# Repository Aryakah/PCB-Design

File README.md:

Hello Everyone,

here i would publish my progress designing PCBs as a beginner. Hope it also helps you.

Im working on both Kicad and Altium projects, be sure you are pulling the right one:)

1 - Stm32f4 – Buck Converter 

2 - Stm32wb55 RF-Anwendung with USB-C 

3 - ESP32-S1 mini WIFI + Bluetooth (Altium)

4 - NRF24l01 Clone (added 04.11.2024)

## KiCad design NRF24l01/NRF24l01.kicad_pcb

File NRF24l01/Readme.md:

NRF24l01 PCB clone on Kicad. Schematics sourced from data Sheet.

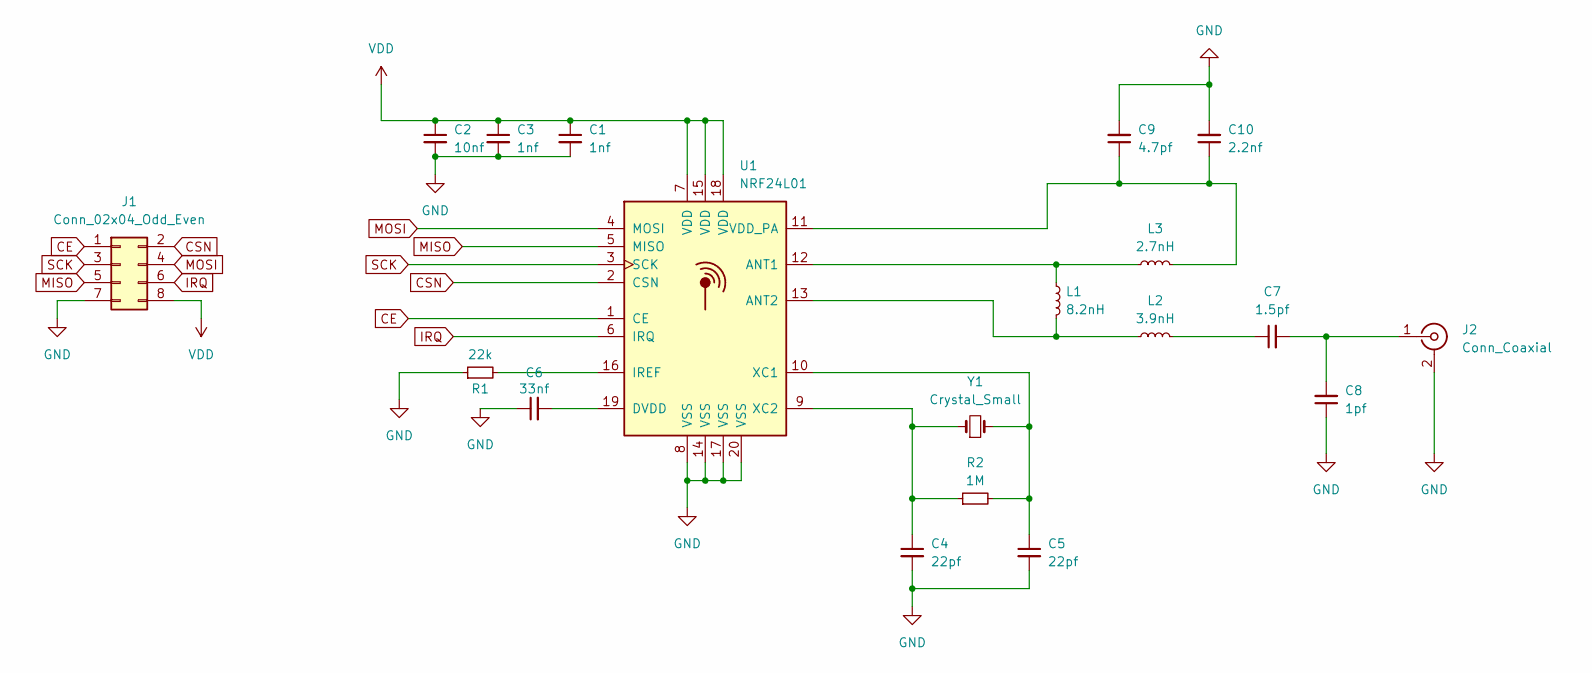
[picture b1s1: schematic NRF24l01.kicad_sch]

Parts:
C1, C3: 1nf; C_0402_1005Metric
C2: 10nf; C_0402_1005Metric
C4, C5: 22pf; C_0402_1005Metric
C6: 33nf; C_0402_1005Metric
C7: 1.5pf; C_0402_1005Metric
C8: 1pf; C_0402_1005Metric
C9: 4.7pf; C_0402_1005Metric
C10: 2.2nf; C_0402_1005Metric
J1: Conn_02x04_Odd_Even; PinHeader_2x04_P1.00mm_Vertical
J2: Conn_Coaxial; MMCX_Molex_73415-1471_Vertical
L1: 8.2nH; L_0402_1005Metric
L2: 3.9nH; L_0402_1005Metric
L3: 2.7nH; L_0402_1005Metric
R1: 22k; R_0402_1005Metric
R2: 1M; R_0402_1005Metric
U1: NRF24L01; QFN-20-1EP_4x4mm_P0.5mm_EP2.5x2.5mm
Y1: Crystal_Small; Crystal_SMD_HC49-SD

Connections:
CE: J1.1, U1.1 (CE)
CSN: J1.2, U1.2 (CSN)
GND: C1.2, C2.2, C3.2, C4.2, C5.2, C6.1, C8.1, C9.2, C10.2, J1.7, J2.2 (Ext), R1.1, U1.8 (VSS), U1.14 (VSS), U1.17 (VSS), U1.20 (VSS)
IRQ: J1.6, U1.6 (IRQ)
MISO: J1.5, U1.5 (MISO)
MOSI: J1.4, U1.4 (MOSI)
unnamed: C7.2, C8.2, J2.1 (In)
unnamed: C7.1, L2.2
unnamed: L1.1, L3.1, U1.12 (ANT1)
unnamed: L1.2, L2.1, U1.13 (ANT2)
unnamed: C6.2, U1.19 (DVDD)
unnamed: R1.2, U1.16 (IREF)
unnamed: C9.1, C10.1, L3.2, U1.11 (VDD_PA)
unnamed: C5.1, R2.2, U1.10 (XC1), Y1.2
unnamed: C4.1, R2.1, U1.9 (XC2), Y1.1
SCK: J1.3, U1.3 (SCK)
VDD: C1.1, C2.1, C3.1, J1.8, U1.7 (VDD), U1.15 (VDD), U1.18 (VDD)

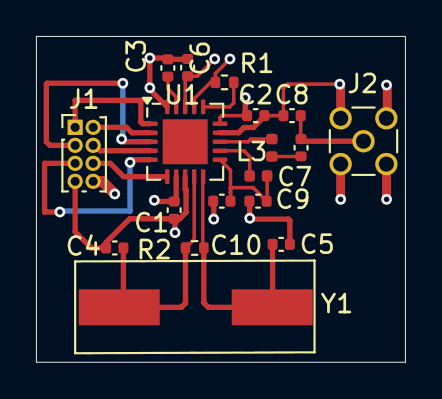
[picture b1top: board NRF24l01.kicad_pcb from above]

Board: 4 copper layers, 20.5 x 18.1 mm, 18 parts (0 on the bottom side), 17 nets.

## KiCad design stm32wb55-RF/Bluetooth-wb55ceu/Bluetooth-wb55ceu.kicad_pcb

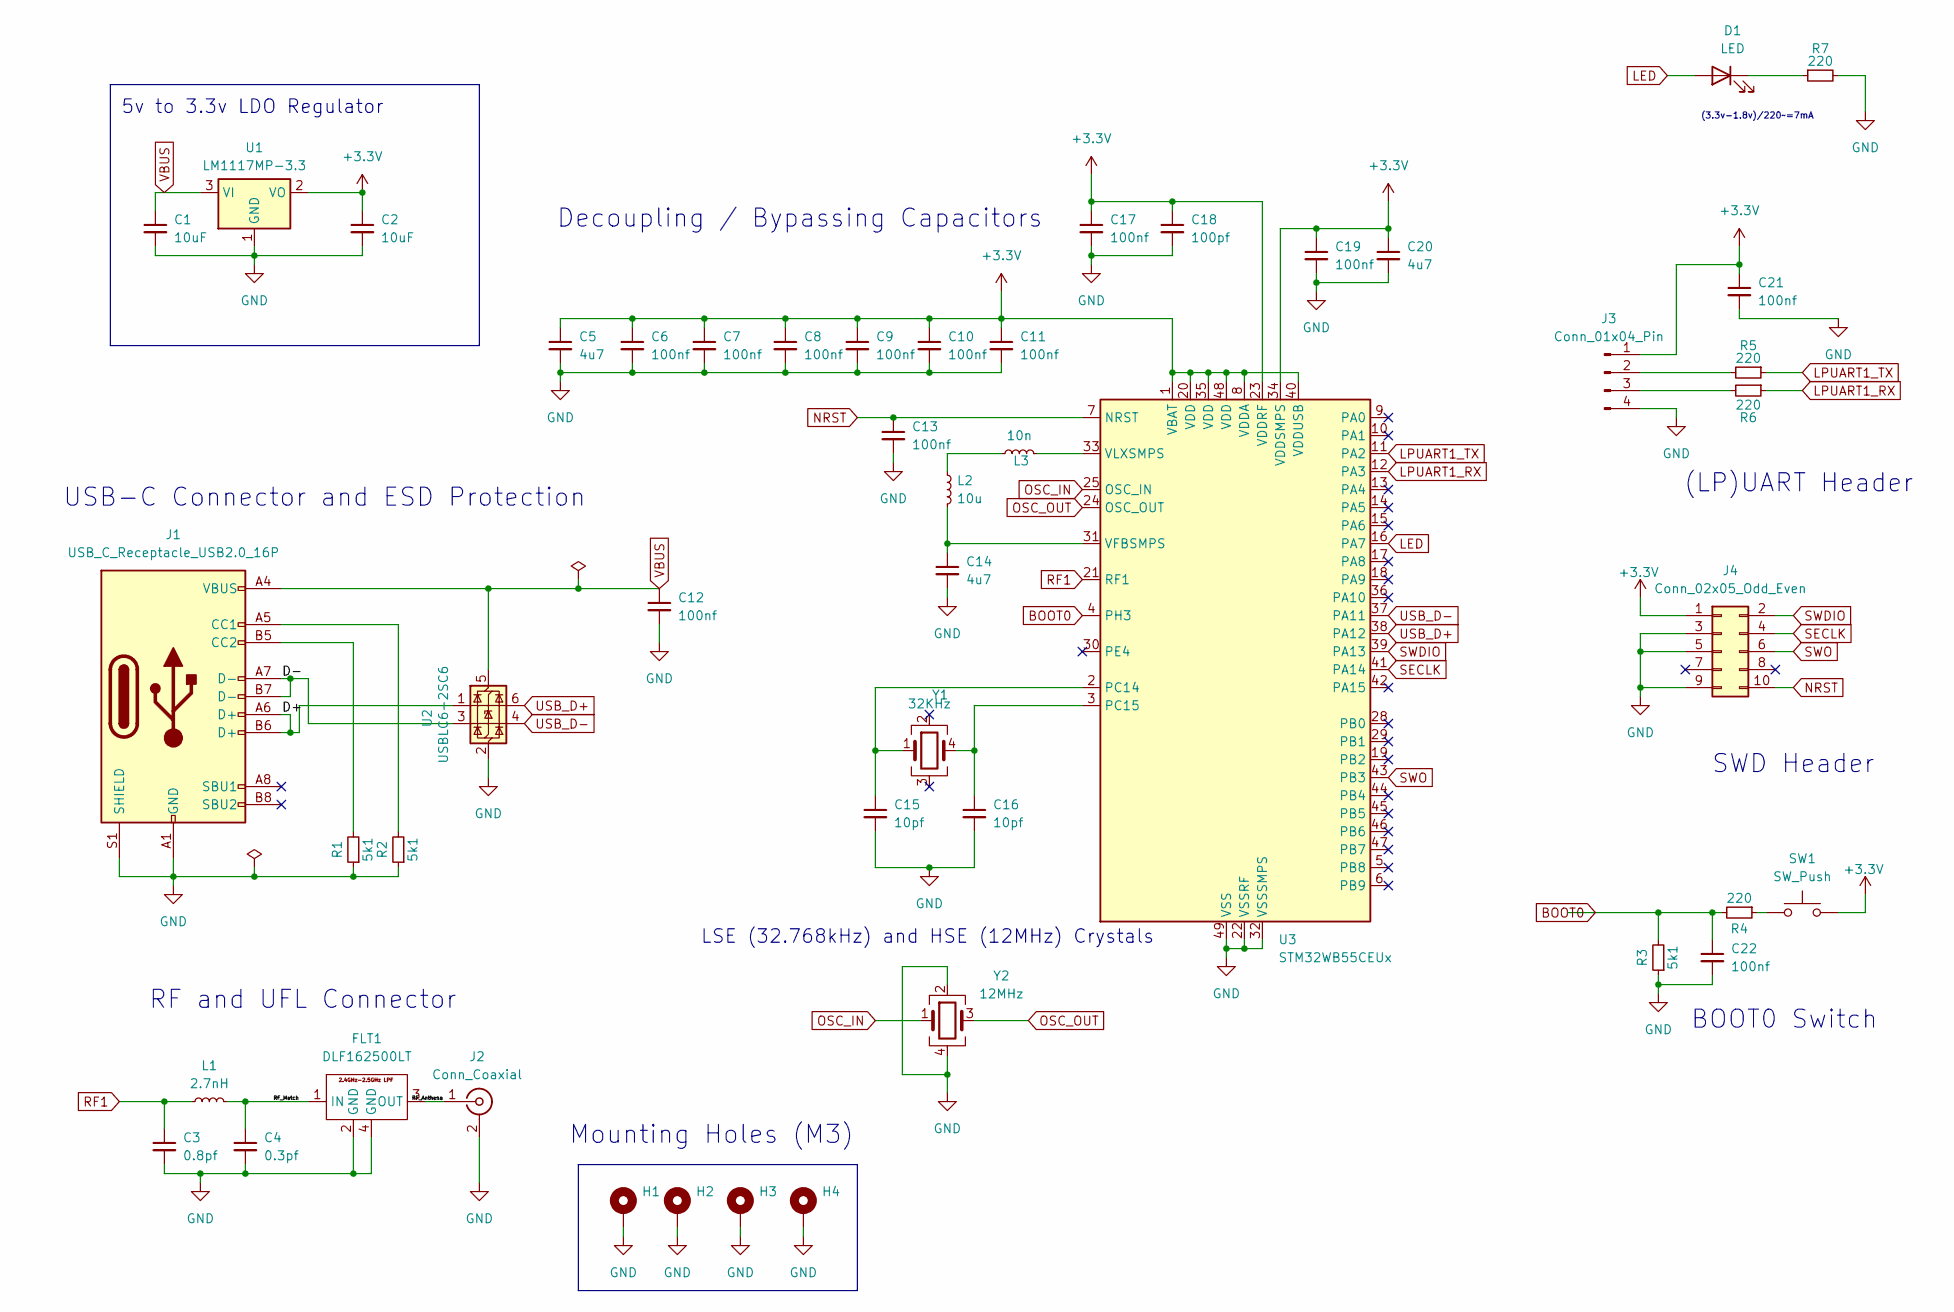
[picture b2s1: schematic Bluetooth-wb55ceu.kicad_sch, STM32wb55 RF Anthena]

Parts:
C1, C2: 10uF; C_1206_3216Metric_Pad1.33x1.80mm_HandSolder
C3: 0.8pf; C_0603_1608Metric_Pad1.08x0.95mm_HandSolder
C4: 0.3pf; C_0603_1608Metric_Pad1.08x0.95mm_HandSolder
C5, C14, C20: 4u7; C_0805_2012Metric_Pad1.18x1.45mm_HandSolder
C6, C7, C8, C9, C10, C11, C12, C13, C17, C19, C21, C22: 100nf; C_0805_2012Metric_Pad1.18x1.45mm_HandSolder
C15, C16: 10pf; C_0805_2012Metric_Pad1.18x1.45mm_HandSolder
C18: 100pf; C_0805_2012Metric_Pad1.18x1.45mm_HandSolder
D1: LED; LED_0805_2012Metric_Pad1.15x1.40mm_HandSolder
FLT1: DLF162500LT
H1, H2, H3, H4: MountingHole_Pad; MountingHole_3.2mm_M3_Pad
J1: USB_C_Receptacle_USB2.0_16P; USB_C_Receptacle_GCT_USB4105-xx-A_16P_TopMnt_Horizontal
J2: Conn_Coaxial; U.FL_Hirose_U.FL-R-SMT-1_Vertical
J3: Conn_01x04_Pin; Molex_PicoBlade_53048-0410_1x04_P1.25mm_Horizontal
J4: Conn_02x05_Odd_Even; JST_PHD_S10B-PHDSS_2x05_P2.00mm_Horizontal
L1: 2.7nH; L_0603_1608Metric_Pad1.05x0.95mm_HandSolder
L2: 10u; L_0805_2012Metric_Pad1.15x1.40mm_HandSolder
L3: 10n; L_0805_2012Metric_Pad1.15x1.40mm_HandSolder
R1, R2, R3: 5k1; R_0805_2012Metric_Pad1.20x1.40mm_HandSolder
R4, R5, R6, R7: 220; R_0805_2012Metric_Pad1.20x1.40mm_HandSolder
SW1: SW_Push; SW_SPST_CK_RS282G05A3
U1: LM1117MP-3.3; SOT-223-3_TabPin2
U2: USBLC6-2SC6; SOT-23-6
U3: STM32WB55CEUx; QFN-48-1EP_7x7mm_P0.5mm_EP5.6x5.6mm
Y1: 32KHz; Crystal_SMD_Abracon_ABS25-4Pin_8.0x3.8mm
Y2: 12MHz; Crystal_SMD_5032-4Pin_5.0x3.2mm

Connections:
+3.3V: C2.1, C5.1, C6.1, C7.1, C8.1, C9.1, C10.1, C11.1, C17.1, C18.1, C19.1, C20.1, C21.1, J3.1, J4.1, SW1.2, U1.2 (VO), U3.1 (VBAT), U3.8 (VDDA), U3.20 (VDD), U3.23 (VDDRF), U3.34 (VDDSMPS), U3.35 (VDD), U3.40 (VDDUSB), U3.48 (VDD)
/D+: J1.A6 (D+), J1.B6 (D+), U2.1 (I/O1)
/D-: J1.A7 (D-), J1.B7 (D-), U2.3 (I/O2)
/RF_Anthena: FLT1.3 (OUT), J2.1 (In)
/RF_Match: C4.1, FLT1.1 (IN), L1.2
BOOT0: C22.1, R3.2, R4.2, U3.4 (PH3)
GND: C1.2, C2.2, C3.2, C4.2, C5.2, C6.2, C7.2, C8.2, C9.2, C10.2, C11.2, C12.2, C13.2, C14.2, C15.2, C16.2, C17.2, C18.2, C19.2, C20.2, C21.2, C22.2, FLT1.2 (GND), FLT1.4 (GND), H1.1, H2.1, H3.1, H4.1, J1.A1 (GND), J1.A12 (GND), J1.B1 (GND), J1.B12 (GND), J1.S1 (SHIELD), J2.2 (Ext), J3.4, J4.3, J4.5, J4.9, R1.1, R2.1, R3.1, R7.2, U1.1 (GND), U2.2 (GND), U3.22 (VSSRF), U3.32 (VSSSMPS), U3.49 (VSS), Y2.2, Y2.4
LED: D1.2 (A), U3.16 (PA7)
LPUART1_RX: R6.1, U3.12 (PA3)
LPUART1_TX: R5.1, U3.11 (PA2)
NRST: C13.1, J4.10, U3.7 (NRST)
unnamed: D1.1 (K), R7.1
unnamed: J1.A5 (CC1), R2.2
unnamed: J1.B5 (CC2), R1.2
unnamed: J3.2, R5.2
unnamed: J3.3, R6.2
unnamed: L2.1, L3.1
unnamed: R4.1, SW1.1
unnamed: C15.1, U3.2 (PC14), Y1.1
unnamed: C16.1, U3.3 (PC15), Y1.4
unnamed: C14.1, L2.2, U3.31 (VFBSMPS)
unnamed: L3.2, U3.33 (VLXSMPS)
OSC_IN: U3.25 (OSC_IN), Y2.1
OSC_OUT: U3.24 (OSC_OUT), Y2.3
RF1: C3.1, L1.1, U3.21 (RF1)
SECLK: J4.4, U3.41 (PA14)
SWDIO: J4.2, U3.39 (PA13)
SWO: J4.6, U3.43 (PB3)
USB_D+: U2.6 (I/O1), U3.38 (PA12)
USB_D-: U2.4 (I/O2), U3.37 (PA11)
VBUS: C1.1, C12.1, J1.A4 (VBUS), J1.A9 (VBUS), J1.B4 (VBUS), J1.B9 (VBUS), U1.3 (VI), U2.5 (VBUS)

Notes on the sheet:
SWD Header
Decoupling / Bypassing Capacitors
(3.3v-1.8v)/220~=7mA
(LP)UART Header
Mounting Holes (M3)
5v to 3.3v LDO Regulator
RF and UFL Connector
LSE (32.768kHz) and HSE (12MHz) Crystals
USB-C Connector and ESD Protection
BOOT0 Switch

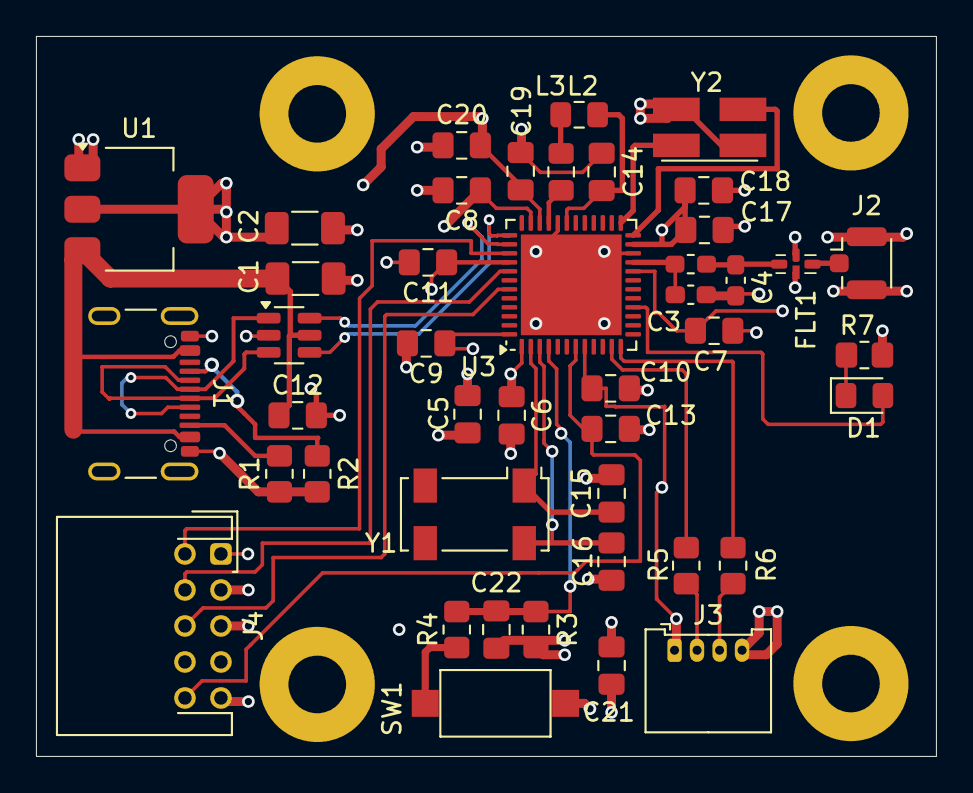
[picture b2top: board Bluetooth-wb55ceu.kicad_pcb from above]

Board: 4 copper layers, 50.0 x 40.0 mm, 48 parts (0 on the bottom side), 31 nets.

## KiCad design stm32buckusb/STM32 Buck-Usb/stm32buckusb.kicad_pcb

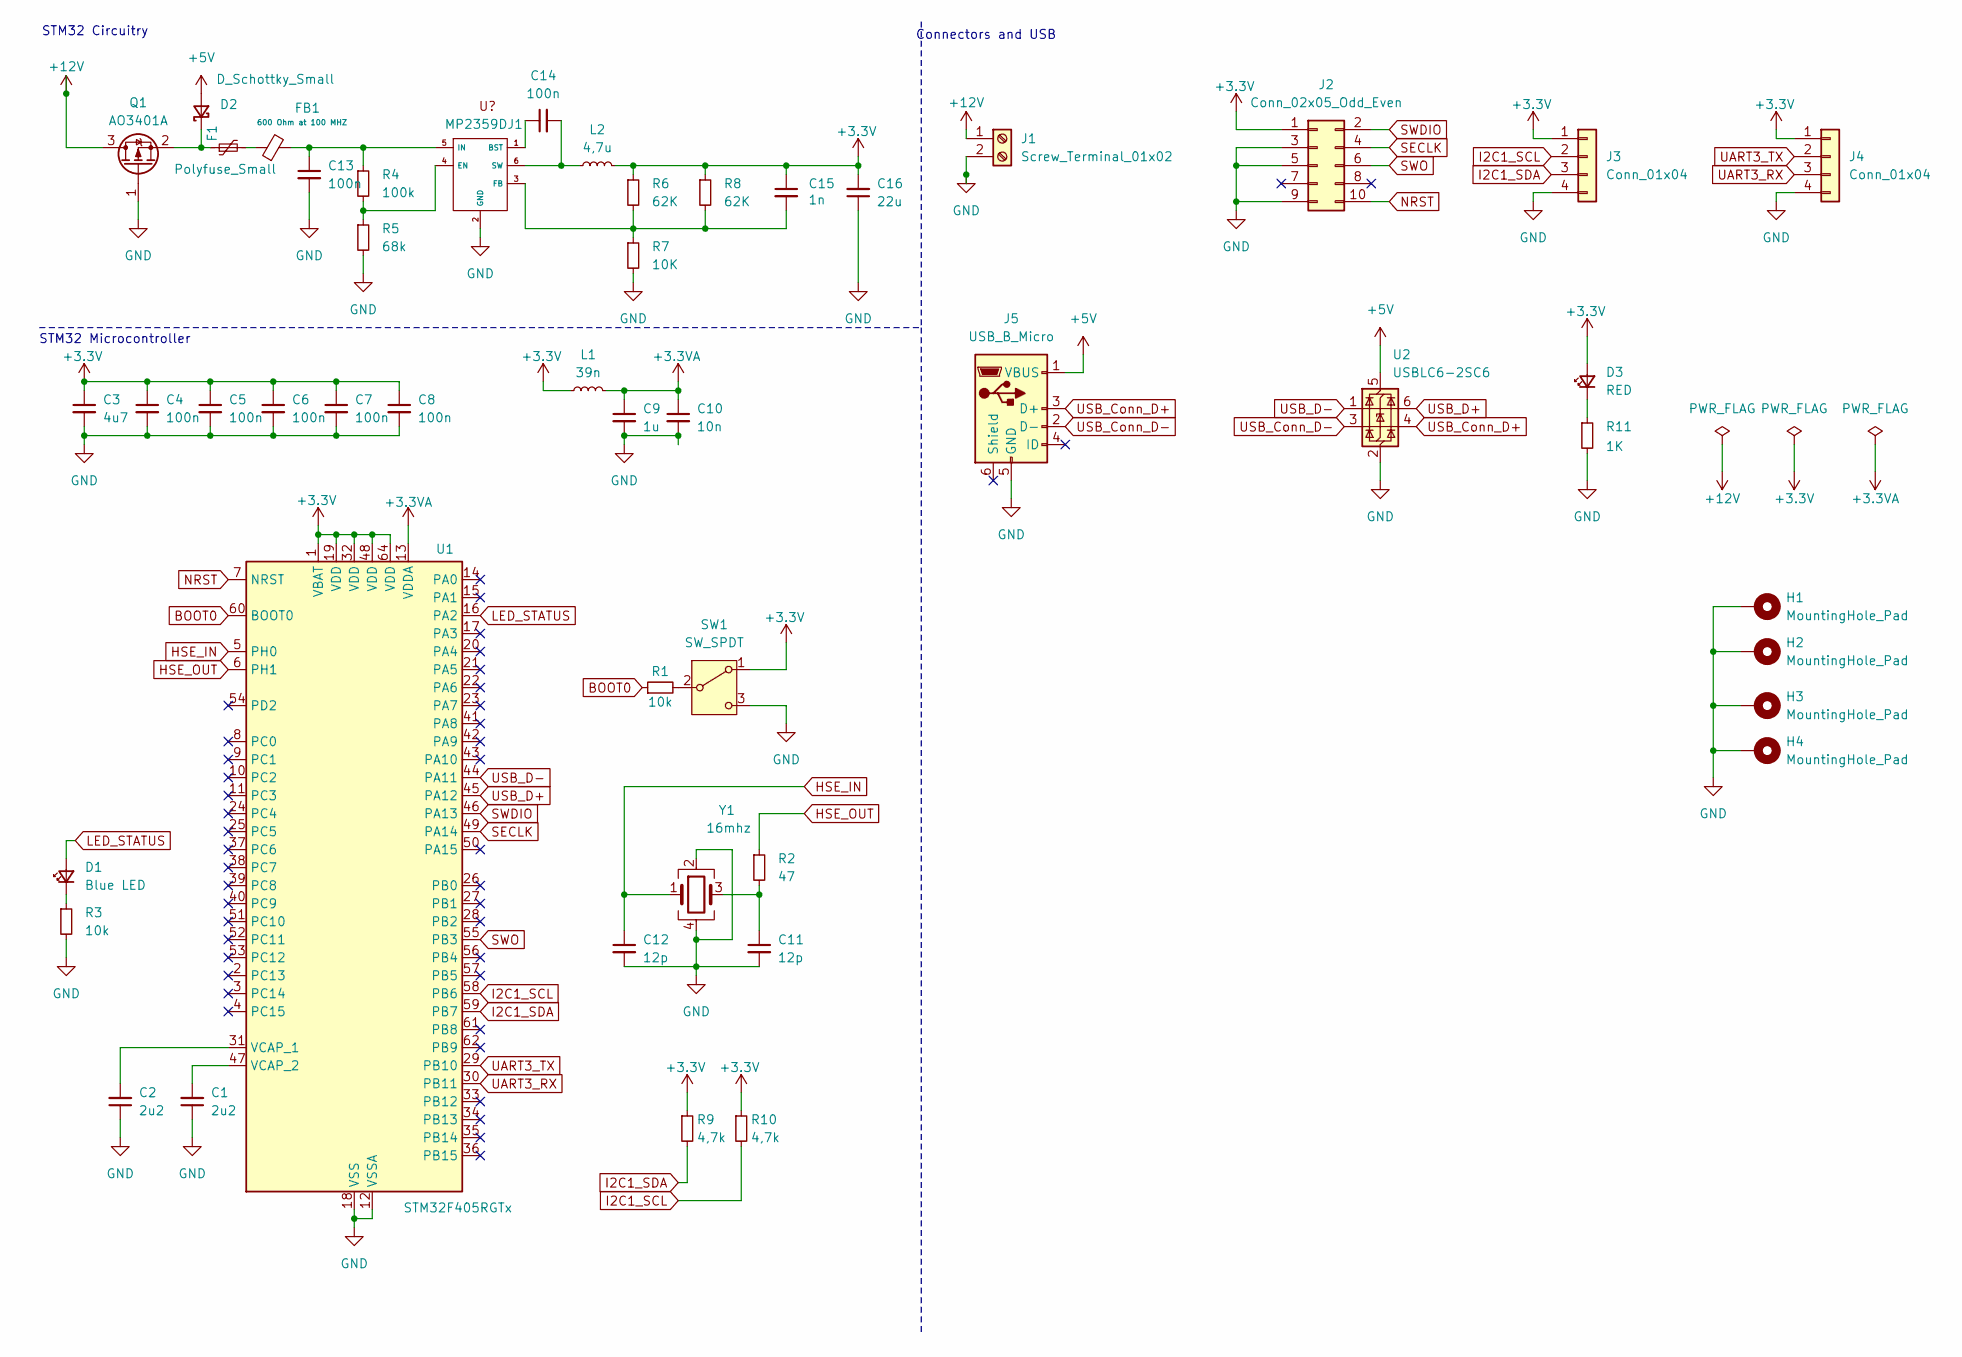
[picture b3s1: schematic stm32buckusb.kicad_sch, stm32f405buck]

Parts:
C1, C2: 2u2; C_0805_2012Metric
C3: 4u7; C_0805_2012Metric
C4, C5, C6, C7, C8, C13, C14: 100n; C_0402_1005Metric
C9: 1u; C_0402_1005Metric
C10: 10n; C_0402_1005Metric
C11, C12: 12p; C_0402_1005Metric
C15: 1n; C_0402_1005Metric
C16: 22u; C_0603_1608Metric
D1: Blue LED; LED_0603_1608Metric
D2: D_Schottky_Small; D_SOD-123
D3: RED; LED_0603_1608Metric
F1: Polyfuse_Small; Fuse_1206_3216Metric
FB1: 600 Ohm at 100 MHZ; L_0805_2012Metric
H1, H2, H3, H4: MountingHole_Pad; MountingHole_4.3mm_M4_Pad_Via
J1: Screw_Terminal_01x02; TerminalBlock_Phoenix_PT-1,5-2-3.5-H_1x02_P3.50mm_Horizontal
J2: Conn_02x05_Odd_Even; PinHeader_2x05_P1.27mm_Vertical
J3, J4: Conn_01x04; Molex_PicoBlade_53048-0410_1x04_P1.25mm_Horizontal
J5: USB_B_Micro; USB_Micro-B_Amphenol_10118193-0001LF_Horizontal
L1: 39n; L_0402_1005Metric
L2: 4,7u; L_0805_2012Metric
MP2359DJ1: SOT-23-6
Q1: AO3401A; SOT-23
R1: 10k; R_0402_1005Metric
R2: 47; R_0402_1005Metric
R3: 10k; R_0603_1608Metric
R4: 100k; R_0603_1608Metric
R5: 68k; R_0603_1608Metric
R6, R8: 62K; R_0603_1608Metric
R7: 10K; R_0603_1608Metric
R9, R10: 4,7k; R_0603_1608Metric
R11: 1K; R_0603_1608Metric
SW1: SW_SPDT; SW_SPDT_PCM12
U1: STM32F405RGTx; LQFP-64_10x10mm_P0.5mm
U2: USBLC6-2SC6; SOT-23-6
Y1: 16mhz; Crystal_SMD_3225-4Pin_3.2x2.5mm

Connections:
+3.3V: C3.1, C4.1, C5.1, C6.1, C7.1, C8.1, C15.1, C16.2, D3.2 (A), J2.1, J3.1, J4.1, L1.1, L2.2, R6.1, R8.1, R9.1, R10.1, SW1.1 (A), U1.1 (VBAT), U1.19 (VDD), U1.32 (VDD), U1.48 (VDD), U1.64 (VDD)
+3.3VA: C9.1, C10.1, L1.2, U1.13 (VDDA)
+5V: D2.2 (A), J5.1 (VBUS), U2.5 (VBUS)
+12V: J1.1, Q1.3 (D)
BOOT0: R1.1, U1.60 (BOOT0)
GND: C1.1, C2.1, C3.2, C4.2, C5.2, C6.2, C7.2, C8.2, C9.2, C10.2, C11.2, C12.2, C13.2, C16.1, H1.1, H2.1, H3.1, H4.1, J1.2, J2.3, J2.5, J2.9, J3.4, J4.4, J5.5 (GND), MP2359DJ1.2 (GND), Q1.1 (G), R3.2, R5.2, R7.2, R11.2, SW1.3 (C), U1.12 (VSSA), U1.18 (VSS), U1.63 (VSS), U2.2 (GND), Y1.2, Y1.4
HSE_IN: C12.1, U1.5 (PH0), Y1.1
HSE_OUT: R2.1, U1.6 (PH1)
I2C1_SCL: J3.2, R10.2, U1.58 (PB6)
I2C1_SDA: J3.3, R9.2, U1.59 (PB7)
LED_STATUS: D1.2 (A), U1.16 (PA2)
NRST: J2.10, U1.7 (NRST)
unnamed: C11.1, R2.2, Y1.3
unnamed: D1.1 (K), R3.1
unnamed: D2.1 (K), F1.1, Q1.2 (S)
unnamed: D3.1 (K), R11.1
unnamed: F1.2, FB1.1
unnamed: C14.1, MP2359DJ1.1 (BST)
unnamed: MP2359DJ1.4 (EN), R4.2, R5.1
unnamed: C15.2, MP2359DJ1.3 (FB), R6.2, R7.1, R8.2
unnamed: C13.1, FB1.2, MP2359DJ1.5 (IN), R4.1
unnamed: C14.2, L2.1, MP2359DJ1.6 (SW)
unnamed: R1.2, SW1.2 (B)
unnamed: C2.2, U1.31 (VCAP_1)
unnamed: C1.2, U1.47 (VCAP_2)
SECLK: J2.4, U1.49 (PA14)
SWDIO: J2.2, U1.46 (PA13)
SWO: J2.6, U1.55 (PB3)
UART3_RX: J4.3, U1.30 (PB11)
UART3_TX: J4.2, U1.29 (PB10)
USB_Conn_D+: J5.3 (D+), U2.4 (I/O2)
USB_Conn_D-: J5.2 (D-), U2.3 (I/O2)
USB_D+: U1.45 (PA12), U2.6 (I/O1)
USB_D-: U1.44 (PA11), U2.1 (I/O1)

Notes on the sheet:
STM32 Circuitry
Connectors and USB
STM32 Microcontroller

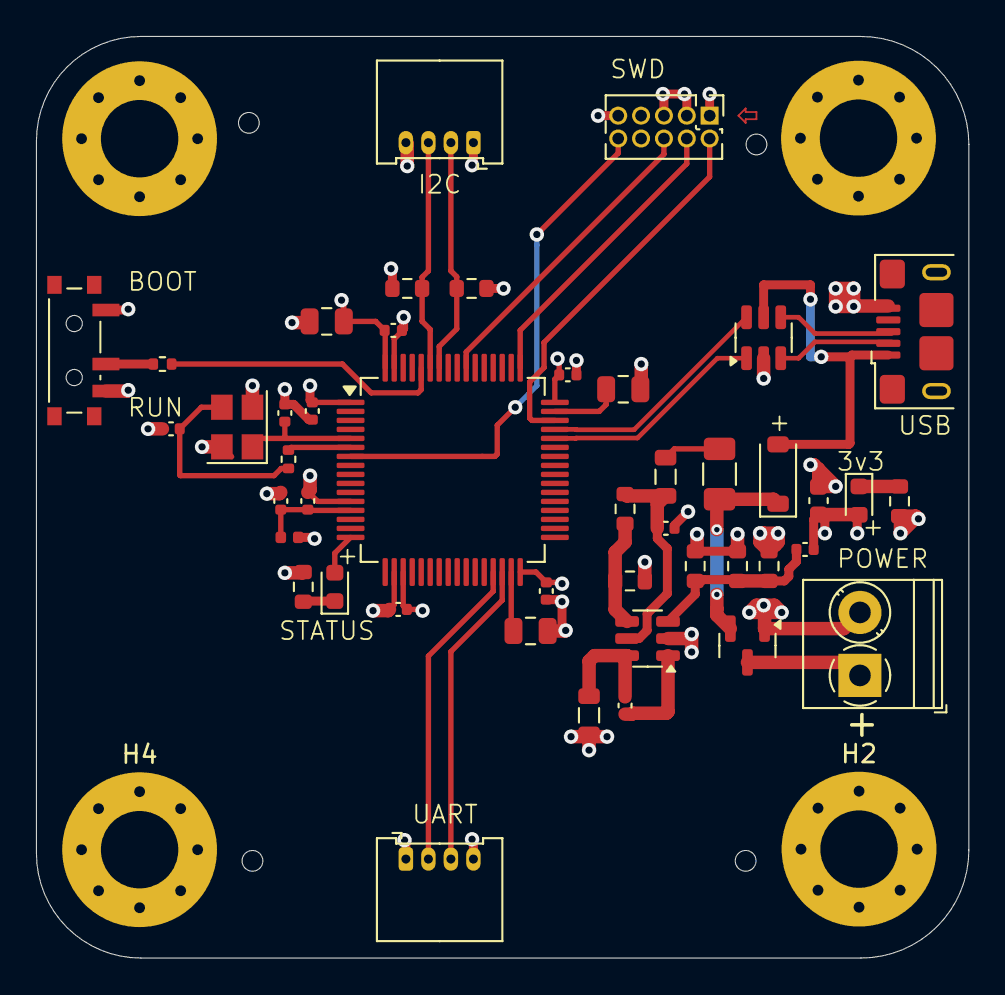
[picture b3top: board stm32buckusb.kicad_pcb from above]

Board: 4 copper layers, 51.8 x 51.2 mm, 49 parts (0 on the bottom side), 34 nets.

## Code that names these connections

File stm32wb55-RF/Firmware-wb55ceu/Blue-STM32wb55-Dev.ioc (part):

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Mcu.Name=STM32WB55CEUx
Mcu.Package=UFQFPN48
Mcu.UserName=STM32WB55CEUx
PA11.Mode=Device
PA11.Signal=USB_DM
PA12.Mode=Device
PA12.Signal=USB_DP
PA13.Mode=Trace_Asynchronous_SW
PA13.Signal=SYS_JTMS-SWDIO
PA14.Mode=Trace_Asynchronous_SW
PA14.Signal=SYS_JTCK-SWCLK
PA2.Mode=Asynchronous
PA2.Signal=LPUART1_TX
PA3.Mode=Asynchronous
PA3.Signal=LPUART1_RX
PA7.Signal=S_TIM17_CH1
PB3.Mode=Trace_Asynchronous_SW
PB3.Signal=SYS_JTDO-SWO
PB6.Mode=I2C
PB6.Signal=I2C1_SCL
PB7.Mode=I2C
PB7.Signal=I2C1_SDA
PC14-OSC32_IN.Mode=LSE-External-Oscillator
PC14-OSC32_IN.Signal=RCC_OSC32_IN
PC15-OSC32_OUT.Mode=LSE-External-Oscillator
PC15-OSC32_OUT.Signal=RCC_OSC32_OUT
RCC.HSE_VALUE=32000000
board=custom

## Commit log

2024-10-01 rev1 push1
2024-10-01 changes made
2024-10-01 Removed extra folders from repository
2024-10-01 updated rename
2024-10-01 Remove extra files from GitHub
2024-10-02 Deleted unnecessary files
2024-10-03 added wb55
2024-10-03 step added small changes
2024-10-06 changes added
2024-10-07 added tracec and vias
2024-10-11 ESP32-S3-1 added
2024-10-13 ESP32 added
2024-10-13 Folder updated
2024-10-13 Created README.md
2024-10-16 Add new folder and files
2024-11-04 NRF24l01 included
2024-11-04 Readme
